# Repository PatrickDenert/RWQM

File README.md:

Abstract- Many water sources in the world are currently contaminated or at risk of
contamination. The purpose of this system is to allow for the remote monitoring of
water sources in order to preserve the health of many communities. Allowing remote
monitoring allows for faster results and constant monitoring of water quality.

For a full documentation of the project then you can read the Remote Water Quality Monotor report pdf listed in the repository.

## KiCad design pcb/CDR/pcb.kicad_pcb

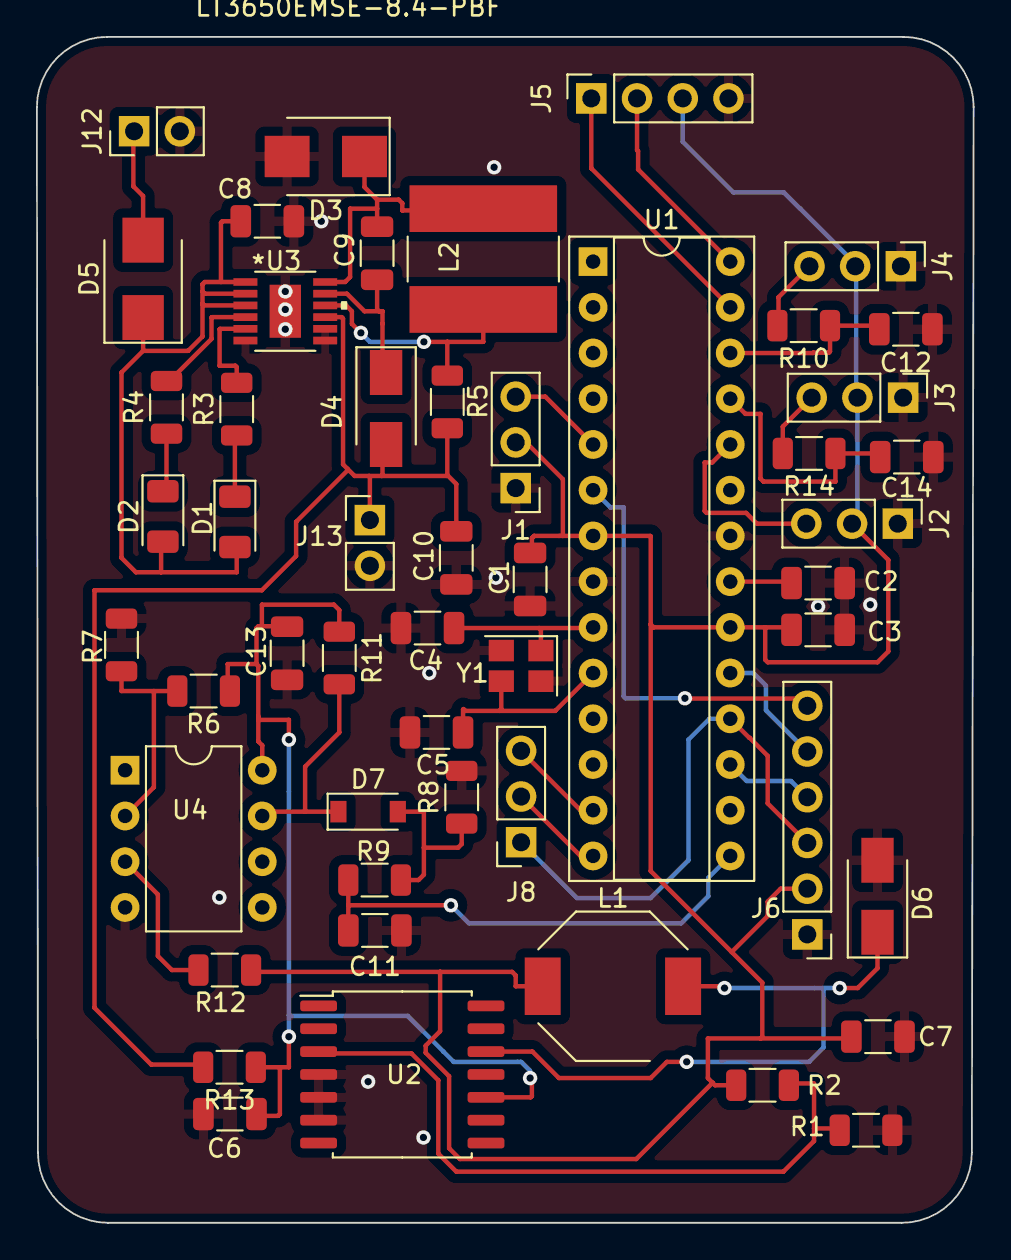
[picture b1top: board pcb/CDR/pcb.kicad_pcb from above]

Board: 2 copper layers, 52.0 x 65.9 mm, 51 parts (0 on the bottom side), 37 nets.

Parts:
C1, C2, C3: 0.1uF; C_1206_3216Metric
C4, C5: 22pF; C_1206_3216Metric
C6: 22uF; C_1206_3216Metric
C7: 220uF; C_1206_3216Metric
C8, C10, C11, C12, C14: 10uF; C_1206_3216Metric
C9, C13: 1uF; C_1206_3216Metric
D1: Red; D_1206_3216Metric
D2: Green; D_1206_3216Metric
D3, D5: CMPSH3-40MA; D_SMB
D4: CMPSH1-4; D_SMA
D6: 11DQ06; D_SMA
D7: 1V; D_SOD-123
J1, J2, J3, J4: Conn_01x03_Male; PinHeader_1x03_P2.54mm_Vertical
J5: Conn_01x04_Female; PinSocket_1x04_P2.54mm_Vertical
J6: SD Card Reader; PinHeader_1x06_P2.54mm_Vertical
J8: cell data headers; PinSocket_1x03_P2.54mm_Vertical
J12: V Solar; PinHeader_1x02_P2.54mm_Vertical
J13: V batt; PinHeader_1x02_P2.54mm_Vertical
L1: 330 uH; L_Bourns-SRU8028_8.0x8.0mm
L2: 10uH; L_Bourns-SRN8040_8x8.15mm
R1: 1K; R_1206_3216Metric
R2: 3.1k; R_1206_3216Metric
R3, R4: 5.1k; R_1206_3216Metric
R5: 0.05; R_1206_3216Metric
R6: 100k; R_1206_3216Metric
R7: 220k; R_1206_3216Metric
R8: 50k; R_1206_3216Metric
R9: 160; R_1206_3216Metric
R10, R14: 0/160; R_1206_3216Metric
R11: 1k; R_1206_3216Metric
R12, R13: 0; R_1206_3216Metric
U1: ATmega328-P; DIP-28_W7.62mm_Socket
U2: LM2574HVM-12; SOIC-14W_7.5x9mm_P1.27mm
U3: LT3650EMSE-8.4-PBF
U4: LM311; DIP-8_W7.62mm
Y1: 16MHz; Crystal_SMD_TXC_7M-4Pin_3.2x2.5mm

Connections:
GND: C1.2, C2.2, C3.1, C4.1, C5.1, C6.2, C7.2, C8.2, C10.2, C11.2, C12.1, C13.1, C14.1, D3.2 (A), D6.2 (A), J1.1, J2.1, J3.1, J4.1, J5.4, J6.1, J12.2, J13.2, R1.1, R7.1, R8.2, U1.8 (GND), U1.22 (GND), U2.4 (SGND), U2.5 (~ON/OFF), U2.6 (PGND), U3.6 (TIMER), U3.7 (RNG/SS), U3.8 (NTC), U3.EPAD, U4.4 (V-), Y1.2, Y1.4
unnamed: C2.1, U1.21 (AREF)
unnamed: C4.2, U1.9 (XTAL1/PB6), Y1.1
unnamed: C5.2, U1.10 (XTAL2/PB7), Y1.3
unnamed: C8.1, D1.2 (A), D2.2 (A), D5.1 (K), U3.1 (VIN), U3.2 (CLP), U3.3 (*SHDN)
unnamed: C9.1, D3.1 (K), L2.2, U3.12 (SW)
unnamed: C9.2, D4.1 (K), U3.11 (BOOST)
unnamed: C10.1, D4.2 (A), J13.1, R5.2, R13.2, U3.9 (BAT)
unnamed: C11.1, R9.2, U1.15 (PB1)
unnamed: C12.2, R10.1, U1.26 (PC3)
unnamed: C6.1, C13.2, R6.1, R11.1, R13.1, U2.10 (VIN), U4.8 (V+)
unnamed: C14.2, R14.1, U1.25 (PC2)
unnamed: D1.1 (K), R3.1
unnamed: D2.1 (K), R4.1
unnamed: D5.2 (A), J12.1
unnamed: D6.1 (K), L1.1, U2.12 (OUT)
unnamed: D7.1 (K), R11.2, U4.7
unnamed: D7.2 (A), R8.1, R9.1
unnamed: J1.3, U1.5 (PD3)
unnamed: J2.3, U1.24 (PC1)
unnamed: J3.3, R14.2
unnamed: J4.3, R10.2
unnamed: J5.1, U1.27 (PC4)
unnamed: J5.2, U1.28 (PC5)
unnamed: J6.3, J8.1, U1.18 (PB4)
unnamed: J6.4, U1.17 (PB3)
unnamed: J6.5, U1.19 (PB5)
unnamed: J6.6, U1.6 (PD4)
unnamed: J8.2, U1.14 (PB0)
unnamed: J8.3, U1.13 (PD7)
unnamed: L2.1, R5.1, U3.10 (SENSE)
unnamed: R1.2, R2.2, U2.3 (FB)
unnamed: R3.2, U3.5 (*FAULT)
unnamed: R4.2, U3.4 (*CHRG)
unnamed: R6.2, R7.2, U4.2 (+)
unnamed: R12.1, U4.3 (-)
VCC: C1.1, C3.2, C7.1, J1.2, J2.2, J3.2, J4.2, J5.3, J6.2, L1.2, R2.1, R12.2, U1.7 (VCC), U1.20 (AVCC)

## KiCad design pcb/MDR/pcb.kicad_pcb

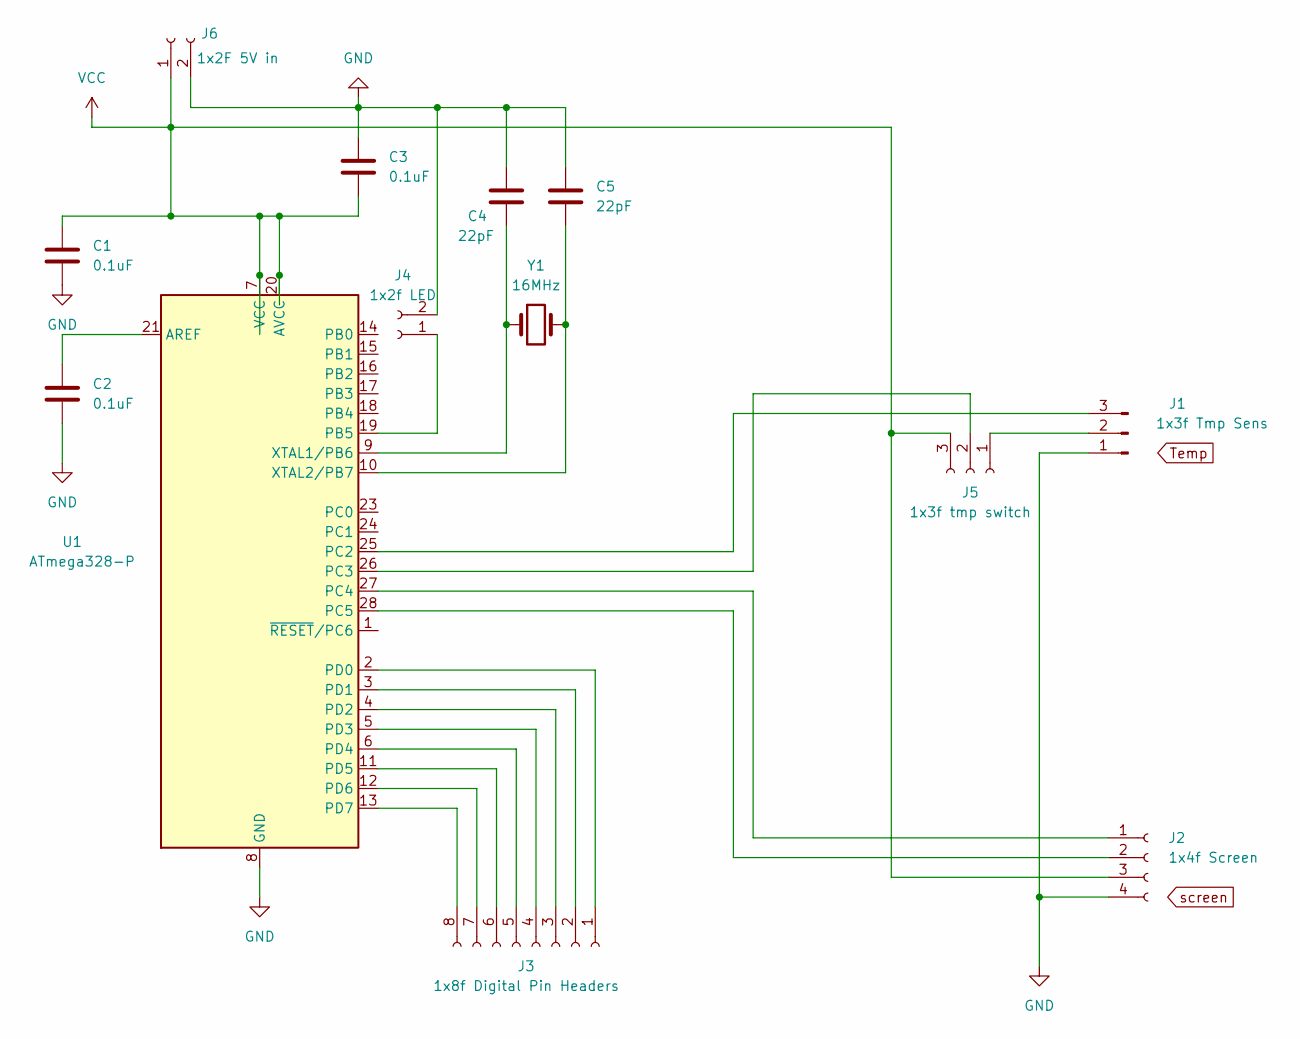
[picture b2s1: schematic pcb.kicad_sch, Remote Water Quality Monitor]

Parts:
C1, C2, C3: 0.1uF; C_1206_3216Metric
C4, C5: 22pF; C_1206_3216Metric
J1: 1x3f Tmp Sens; PinSocket_1x03_P2.54mm_Vertical
J2: 1x4f Screen; PinSocket_1x04_P2.54mm_Vertical
J3: 1x8f Digital Pin Headers; PinSocket_1x08_P2.54mm_Vertical
J4: 1x2f LED; PinHeader_1x02_P2.54mm_Vertical
J5: 1x3f tmp switch; PinSocket_1x03_P2.54mm_Vertical
J6: 1x2F 5V in; PinHeader_1x02_P2.54mm_Vertical
U1: ATmega328-P; DIP-28_W7.62mm_Socket
Y1: 16MHz; Crystal_SMD_3225-4Pin_3.2x2.5mm

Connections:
GND: C1.2, C2.2, C3.1, C4.1, C5.1, J1.1, J2.4, J4.2, J6.2, U1.8 (GND), U1.22 (GND)
unnamed: C2.1, U1.21 (AREF)
unnamed: C4.2, U1.9 (XTAL1/PB6), Y1.1
unnamed: C5.2, U1.10 (XTAL2/PB7), Y1.2
unnamed: J1.2, J5.1
unnamed: J2.1, U1.27 (PC4)
unnamed: J2.2, U1.28 (PC5)
unnamed: J3.1, U1.2 (PD0)
unnamed: J3.2, U1.3 (PD1)
unnamed: J3.3, U1.4 (PD2)
unnamed: J3.4, U1.5 (PD3)
unnamed: J3.5, U1.6 (PD4)
unnamed: J3.6, U1.11 (PD5)
unnamed: J3.7, U1.12 (PD6)
unnamed: J3.8, U1.13 (PD7)
unnamed: J4.1, U1.19 (PB5)
unnamed: J1.3, U1.25 (PC2)
unnamed: J5.2, U1.26 (PC3)
VCC: C1.1, C3.2, J2.3, J5.3, J6.1, U1.7 (VCC), U1.20 (AVCC)

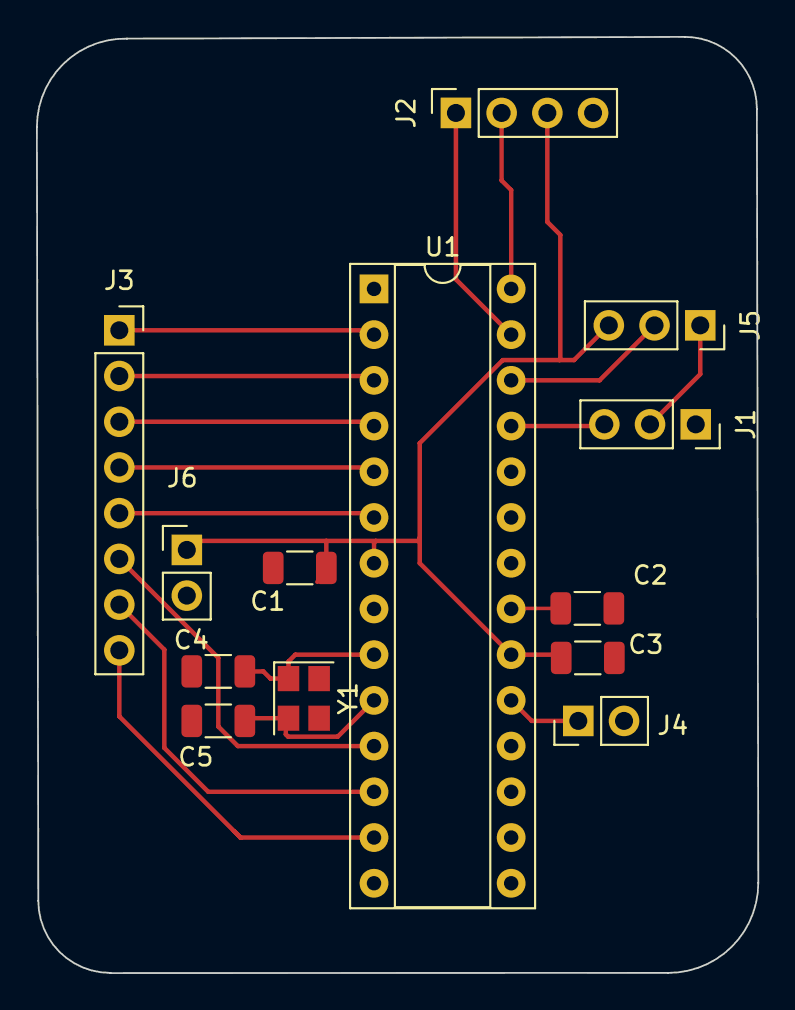
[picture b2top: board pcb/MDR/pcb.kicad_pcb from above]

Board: 2 copper layers, 40.1 x 52.0 mm, 13 parts (0 on the bottom side), 19 nets.

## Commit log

2022-10-24 init
2022-10-31 initial pcb
2022-11-07 web stuff
2022-11-07 seperate server
2022-11-07 nicer charts
2022-11-08 file tree restructure
2022-11-08 file tree restructuring
2022-11-08 log host and port
2022-11-08 fix sensor data requst url
2022-11-08 change start command
2022-11-09 pcb update
2022-12-08 fixed the app
2022-12-08 max old space size
2022-12-08 netlify
2023-03-06 cdr pcb
2023-03-06 API and analytics scaffolding
2023-03-06 pcb and analytics updates
2023-03-06 decoupling cap on lm 311
2023-03-17 major updates to interface, analytics and security
2023-03-18 minor updates, bug fixesand stuff
2023-03-20 Add files via upload
    libraries
2023-03-20 Update cdr.ino
    fixed error code generation and hash and encryption
2023-03-21 end to end pipleine for demo
2023-03-23 readings from arduino show up in database and charts
2023-03-23 cleaned middleware code, moved files
2023-03-23 logging for demo in serial file
2023-03-27 updated TDS function to save mem
2023-03-28 CDR preliminary demo file
2023-04-12 reduced 6% memory from cdr by moving variable definitions
2023-04-25 Create endtoend.ino
    sends error code and sensor data from actual sensors but there is an error atm where it stops after 1 loop
2023-04-28 1284 test connection
2023-04-30 Create fprdemo
    added SD module support
2023-05-05 Update fpr2.ino
    reduced delay
2023-05-08 Create httptest
    test http connection for api
2023-05-08 Update fpr2.ino
    got real time from api
    fixed SD module
2023-05-08 Update fpr2.ino
    fixed time issue and alert params
2023-05-08 Update fpr2.ino
    updated time zone abd alert code
2023-05-08 Update fpr2.ino
    added comments and increased readability
2023-05-08 Rename 1284connectiontest.ino to MCU code/1284connectiontest.ino
2023-05-08 Rename cdr.ino to MCU code/cdrdemo.ino
2023-05-08 Rename endtoend.ino to MCU code/endtoend.ino
2023-05-08 Rename fpr2.ino to MCU code/fpr.ino
2023-05-08 Rename team1FPRdemo.ino to FPR Demo/team1FPRdemo.ino
2023-05-12 recent changes
2024-01-03 fix formatting
2024-01-03 rename folder
2024-01-03 add report

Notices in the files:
parts and their libraries:
Copyright 2021 Accelerated Designs. All rights reserved.
